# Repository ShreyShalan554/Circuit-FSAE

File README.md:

# Circuit-FSAE

This repo include all the file such as schematic, pcb layout, 3D design, gerbers of all the safety circuits used in our Formula Bharat competing race car.

# Software-Used

KiCAD

# Description of circuits

1.Charger Shutdown Circuit

2.Shutdown Circuit

3.Precharge Circuit

4.Tractive System Active Light

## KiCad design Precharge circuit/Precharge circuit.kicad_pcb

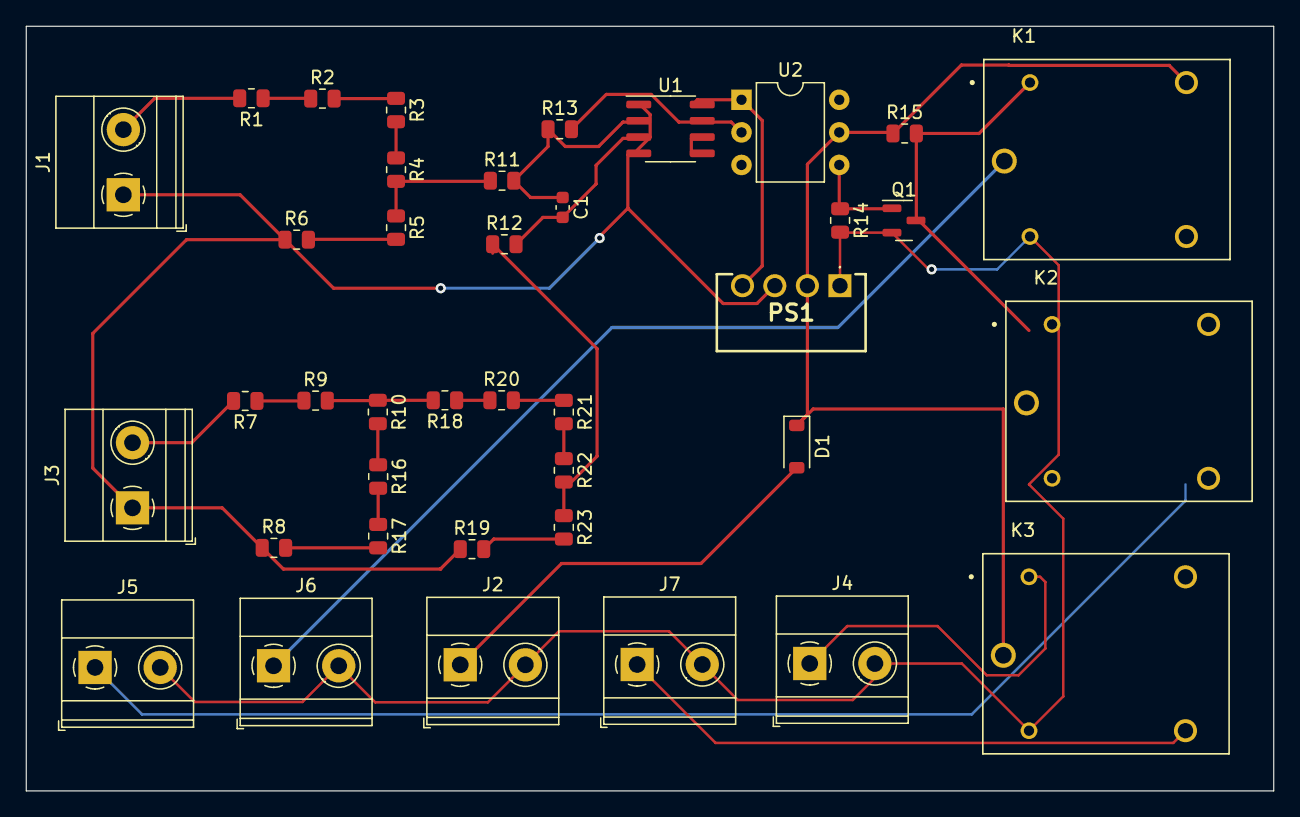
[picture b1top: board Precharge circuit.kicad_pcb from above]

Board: 2 copper layers, 97.3 x 59.6 mm, 39 parts (0 on the bottom side), 32 nets.

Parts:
C1: 10n; C_0603_1608Metric
D1: 1N4148W; D_SOD-123
J1, J3: Conn_01x02_Socket; TerminalBlock_Phoenix_MKDS-1,5-2-5.08_1x02_P5.08mm_Horizont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
J2, J4, J5, J6, J7: Screw_Terminal_01x02; TerminalBlock_Phoenix_MKDS-1,5-2-5.08_1x02_P5.08mm_Horizont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
K1, K2, K3: SRD-12VDC-SL-C; RELAY_SRD-12VDC-SL-C
PS1: IEB0112S12
Q1: 2N7002; SOT-23
R1, R2, R10, R16, R18, R20: 120k; R_0805_2012Metric
R3, R21: 82k; R_0805_2012Metric
R4, R22: 2k; R_0805_2012Metric
R5, R6, R19, R23: 1k; R_0805_2012Metric
R7, R9, R14: 10k; R_0805_2012Metric
R8: 60k; R_0805_2012Metric
R11, R12: 100; R_0805_2012Metric
R13: 1M; R_0805_2012Metric
R15: 22k; R_0805_2012Metric
R17: 80k; R_0805_2012Metric
U1: LM311; SOIC-8_3.9x4.9mm_P1.27mm
U2: 4N35; DIP-6_W7.62mm

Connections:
+12V: PS1.4 (+VOUT), U1.8 (V+), U2.1
AIR+: J5.1, K2.NO
AIR-: J7.1, K3.NO
GND: J1.1, J3.1, PS1.3 (-VOUT), R6.1, R8.1, R19.1, U1.1 (GND), U1.4 (V-)
unnamed: D1.2 (A), J2.1
unnamed: J1.2, R1.2
unnamed: J3.2, R7.2
unnamed: Q1.1 (G), R14.1, U2.4
unnamed: R1.1, R2.1
unnamed: R2.2, R3.1
unnamed: R3.2, R4.1
unnamed: R5.2, R6.2
unnamed: R7.1, R9.1
unnamed: R9.2, R10.1, R18.2
unnamed: R10.2, R16.1
unnamed: R4.2, R5.1, R11.1
unnamed: R12.1, R22.2, R23.1
unnamed: R13.2, U1.7, U2.2
unnamed: R16.2, R17.1
unnamed: R8.2, R17.2
unnamed: R18.1, R20.1
unnamed: R19.2, R23.2
unnamed: R20.2, R21.1
unnamed: R21.2, R22.1
unnamed: C1.1, R11.2, R13.1, U1.2 (+)
unnamed: C1.2, R12.2, U1.3 (-)
unnamed: U1.5 (BAL), U1.6 (STRB)
SDC+: J4.1, K3.COIL1
SDC-: J2.2, J4.2, J5.2, J6.2, J7.2, K1.COIL2, K2.COIL2, K3.COIL2, PS1.1 (-VIN), Q1.2 (S), R14.2
VCC: D1.1 (K), K1.NC, K2.COM, K3.COM, PS1.2 (+VIN), R15.1, U2.5
precharge: J6.1, K1.COM
rpower: K1.COIL1, K2.COIL1, Q1.3 (D), R15.2

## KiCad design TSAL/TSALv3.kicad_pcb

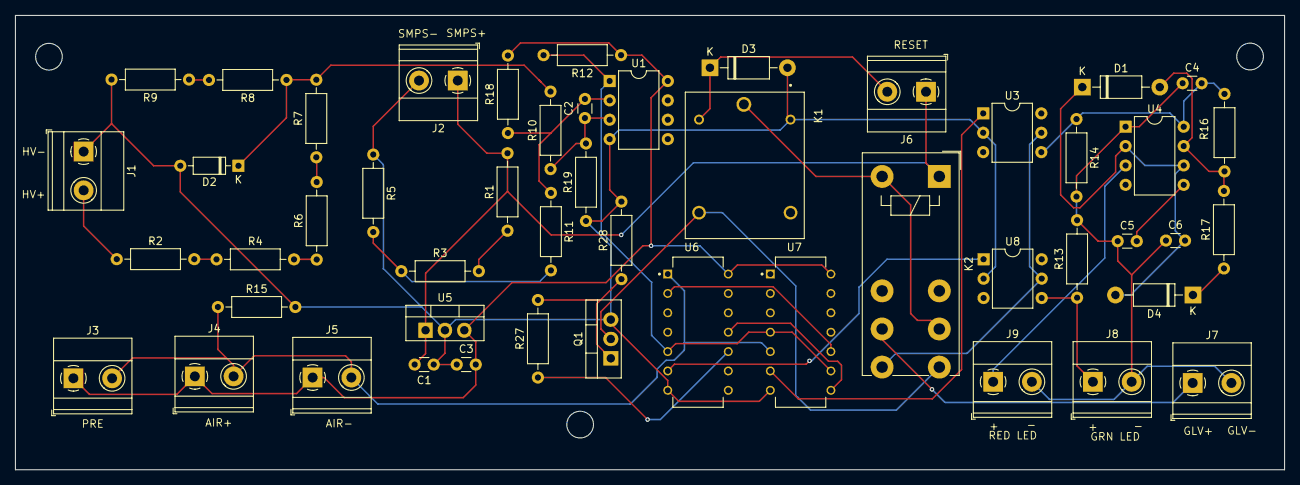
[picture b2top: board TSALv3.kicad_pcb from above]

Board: 2 copper layers, 166.4 x 59.6 mm, 50 parts (0 on the bottom side), 34 nets.

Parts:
C1: 0.33u; C_Disc_D3.0mm_W1.6mm_P2.50mm
C2: 10n; C_Disc_D3.0mm_W1.6mm_P2.50mm
C3: 0.1u; C_Disc_D3.0mm_W1.6mm_P2.50mm
C4, C5: 100n; C_Disc_D3.0mm_W1.6mm_P2.50mm
C6: 1u; C_Disc_D3.0mm_W1.6mm_P2.50mm
D1, D3, D4: 1N4002; D_DO-41_SOD81_P10.16mm_Horizontal
D2: 12V; D_DO-35_SOD27_P7.62mm_Horizontal
J1, J2, J3, J4, J5, J6, J7, J8, J9: Screw_Terminal_01x02; TerminalBlock_Phoenix_MKDS-1,5-2-5.08_1x02_P5.08mm_Horizont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
K1: SRD-12VDC-SL-C; RELAY_SRD-12VDC-SL-C
K2: FINDER-40.52; Relay_DPDT_Finder_40.52
Q1: IRF540N; TO-220-3_Vertical
R1, R13, R14, R15, R28: 10k; R_Axial_DIN0207_L6.3mm_D2.5mm_P10.16mm_Horizontal
R2, R4, R6: 47k; R_Axial_DIN0207_L6.3mm_D2.5mm_P10.16mm_Horizontal
R3, R8, R9, R12, R18, R19: 1k; R_Axial_DIN0207_L6.3mm_D2.5mm_P10.16mm_Horizontal
R5: 1K; R_Axial_DIN0207_L6.3mm_D2.5mm_P10.16mm_Horizontal
R7: 249k; R_Axial_DIN0207_L6.3mm_D2.5mm_P10.16mm_Horizontal
R10, R11, R27: 100; R_Axial_DIN0207_L6.3mm_D2.5mm_P10.16mm_Horizontal
R16, R17: 180k; R_Axial_DIN0207_L6.3mm_D2.5mm_P10.16mm_Horizontal
U1: LM393; DIP-8_W7.62mm
U3, U8: 4N35; DIP-6_W7.62mm
U4: NE555P; DIP-8_W7.62mm
U5: L7805; TO-220-3_Vertical
U6: SN74LS04N; DIP794W45P254L1969H508Q14
U7: SN74LS08N; DIP794W45P254L1969H508Q14

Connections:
+5V: C3.2, J3.1, J4.1, J5.1, R12.1, R18.2, U1.8 (V+), U5.3 (OUT), U6.14 (VCC), U7.14 (VCC)
+12V: C1.2, J2.1, J6.1, K2.A1, R1.2, U5.1 (IN)
/+HV: J1.2, R2.1
/GRN+: J8.1, R13.1, U8.4
/RED+: J9.1, U4.3 (Q)
/Vin: D2.1 (K), R7.2, R8.1, R10.2
/Vref: R3.1, R5.2, R11.2
AIR State: J3.2, J4.2, J5.2, R15.1, U6.1 (1A), U7.5 (2B)
AUX Open: U6.2 (1Y), U7.10 (3B)
GLV supply: K2.24, U3.5, U8.5
GLV+: J7.1, K2.21
GLV-: C4.1, C5.1, C6.1, J7.2, J8.2, J9.2, R13.2, R14.2, U4.1 (GND)
GND: C1.1, C3.1, D2.2 (A), D3.2 (A), J1.1, J2.2, K1.COIL1, Q1.3 (S), R5.1, R9.2, R15.2, R19.1, R28.2, U1.4 (V-), U3.2, U5.2 (GND), U6.7 (GND), U7.7 (GND), U8.2
unnamed: D1.2 (A), R16.1, R17.2, U4.7 (DIS)
unnamed: C6.2, D1.1 (K), D4.2 (A), U4.2 (TR), U4.6 (THR)
unnamed: D4.1 (K), R17.1
unnamed: K1.COM, K2.11, K2.A2
unnamed: K1.NO, K2.14, Q1.2 (D)
unnamed: Q1.1 (G), R27.2, R28.1
unnamed: R1.1, R3.2
unnamed: R2.2, R4.1
unnamed: R4.2, R6.1
unnamed: R6.2, R7.1
unnamed: R8.2, R9.1
unnamed: C2.1, R10.1, R19.2, U1.3 (+)
unnamed: C2.2, R11.1, R18.1, U1.2 (-)
unnamed: C5.2, U4.5 (CV)
unnamed: C4.2, R14.1, R16.2, U3.4, U4.8 (VCC)
RED ON: U3.1, U7.6 (2Y)
TS Status: R12.2, U1.1, U6.5 (3A), U7.4 (2A), U7.9 (3A)
TS' Status: U6.6 (3Y), U8.1
TSAL Error: U6.11 (5A), U7.8 (3Y)
TSAL Error': R27.1, U6.10 (5Y)
reset: D3.1 (K), J6.2, K1.COIL2

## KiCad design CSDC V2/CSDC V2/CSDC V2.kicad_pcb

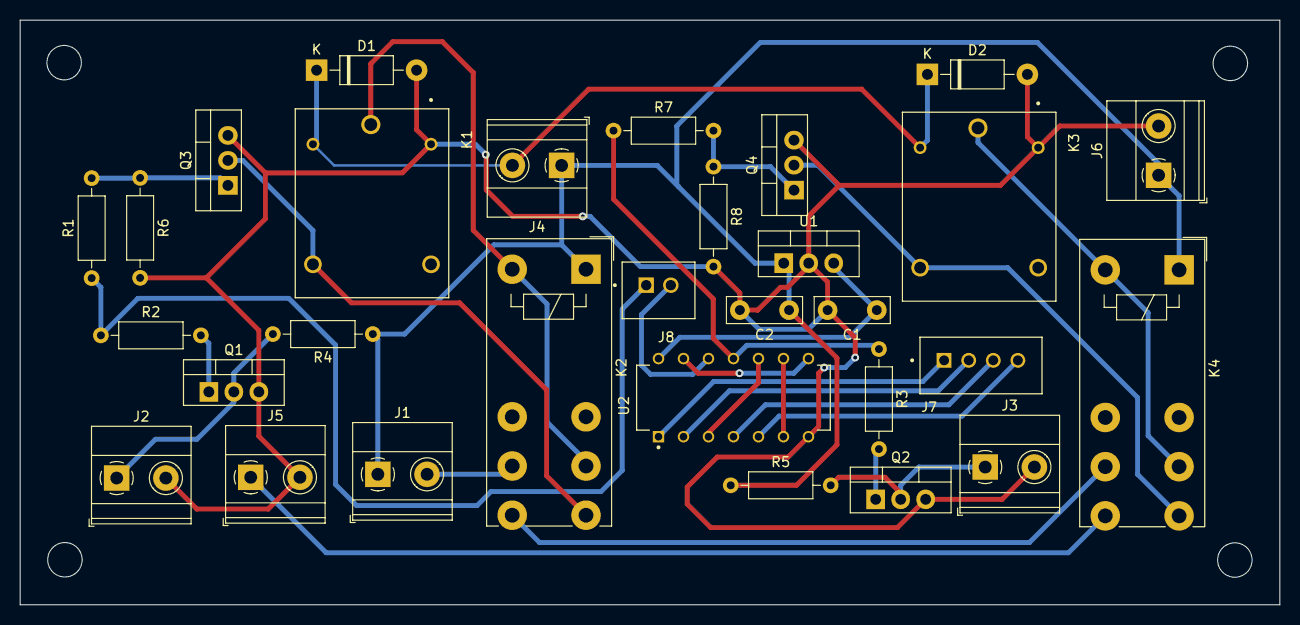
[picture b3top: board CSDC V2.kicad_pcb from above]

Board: 2 copper layers, 128.0 x 59.4 mm, 30 parts (0 on the bottom side), 27 nets.

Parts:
C1: 0.33uf; C_Disc_D7.5mm_W2.5mm_P5.00mm
C2: 0.1uf; C_Disc_D7.5mm_W2.5mm_P5.00mm
D1, D2: 1N4007; D_DO-41_SOD81_P10.16mm_Horizontal
J1, J2, J3, J4, J5, J6: Screw_Terminal_01x02; TerminalBlock_Phoenix_MKDS-1,5-2_1x02_P5.00mm_Horizontal
J7: B4B-XH-A_LF__SN_; JST_B4B-XH-A_LF__SN_
J8: B2B-XH-A_LF__SN_; JST_B2B-XH-A_LF__SN_
K1, K3: SRD-12VDC-SL-C; RELAY_SRD-12VDC-SL-C
K2, K4: FINDER-40.52; Relay_DPDT_Finder_40.52
Q1, Q2, Q3, Q4: IRF540N; TO-220-3_Vertical
R1, R2, R3, R7: 100; R_Axial_DIN0207_L6.3mm_D2.5mm_P10.16mm_Horizontal
R4, R5: 2K; R_Axial_DIN0207_L6.3mm_D2.5mm_P10.16mm_Horizontal
R6, R8: 10k; R_Axial_DIN0207_L6.3mm_D2.5mm_P10.16mm_Horizontal
U1: L7805; TO-220-3_Vertical
U2: SN74LS32N; DIP794W45P254L1969H508Q14

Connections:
+5V: C1.1, U1.3 (OUT), U2.14 (VCC)
AMS Fault: R3.1, R7.1, U2.11 (4Y)
AMS In: K2.24, K4.21
Aux Battery in: C2.1, J1.1, J4.1, J6.1, K2.A1, K4.A1, R4.1, R5.1, U1.1 (IN)
BMS1: J7.1, U2.1 (1A)
BMS2: J7.2, U2.2 (1B)
BMS3: J7.3, U2.4 (2A)
BMS4: J7.4, U2.5 (2B)
BMS5: J8.2, U2.12 (4A)
CSDC+: J5.1, K4.24
CSDC-: C1.2, C2.2, D1.2 (A), D2.2 (A), J2.2, J3.2, J5.2, J6.2, K1.COIL1, K3.COIL1, Q1.3 (S), Q2.3 (S), Q3.3 (S), Q4.3 (S), R6.2, R8.2, U1.2 (GND), U2.7 (GND)
IMD Fault: J8.1, R1.1, R2.1
IMD In: J1.2, K2.21
unnamed: J2.1, Q1.2 (D), R4.2
unnamed: J3.1, Q2.2 (D), R5.2
unnamed: K1.COM, K2.11, K2.A2
unnamed: K3.COM, K4.11, K4.A2
unnamed: Q1.1 (G), R2.2
unnamed: Q2.1 (G), R3.2
unnamed: K1.NO, K2.14, Q3.2 (D)
unnamed: Q3.1 (G), R1.2, R6.1
unnamed: K3.NO, K4.14, Q4.2 (D)
unnamed: Q4.1 (G), R7.2, R8.1
out1: U2.3 (1Y), U2.10 (3B)
out2: U2.6 (2Y), U2.9 (3A)
out3: U2.8 (3Y), U2.13 (4B)
reset: D1.1 (K), D2.1 (K), J4.2, K1.COIL2, K3.COIL2
